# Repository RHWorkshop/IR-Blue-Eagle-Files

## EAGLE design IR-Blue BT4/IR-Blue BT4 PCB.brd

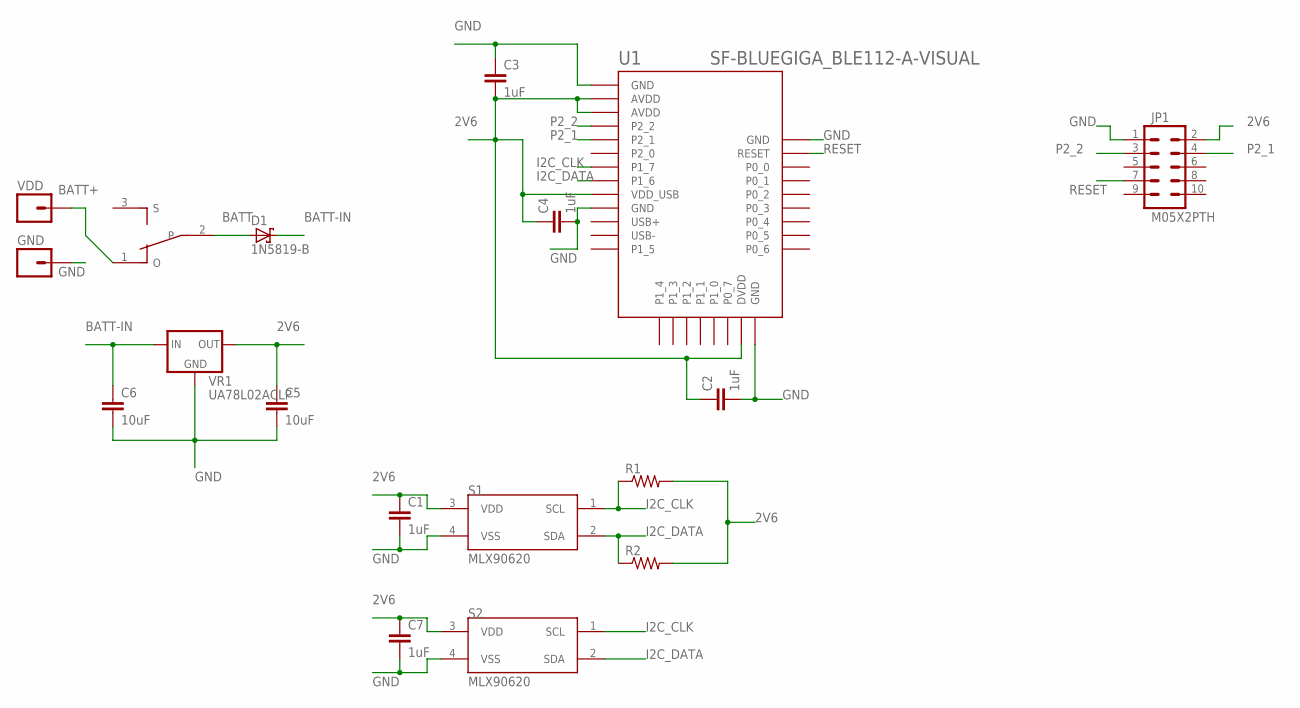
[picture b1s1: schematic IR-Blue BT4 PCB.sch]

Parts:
C1, C2, C3, C4, C7: 1uF; CAP-PTH-5MM
C5, C6: 10uF; CAP-PTH-5MM
D1: 1N5819-B; DO41-7.6
GND: M01PTH; 1X01
JP1: M05X2PTH; AVR_ICSP
R1, R2: RESISTORPTH-1/4W; AXIAL-0.4
S1, S2: MLX90620; TO-39
SW1: SMALL_SWITCH; EG1213
U1: SF-BLUEGIGA_BLE112-A-VISUAL; SF-BLUEGIGA_BLE112-A
VDD: M01PTH; 1X01
VR1: UA78L02ACLP; TO-92

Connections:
2V6: C1.1, C2.1, C3.2, C4.1, C5.1, C7.1, JP1.2, R1.P$2 (2), R2.P$2 (2), S1.3 (VDD), S2.3 (VDD), U1.AVDD1 (AVDD), U1.AVDD2 (AVDD), U1.DVDD, U1.VDD_USB, VR1.1 (OUT)
BATT: D1.A, SW1.2
BATT+: SW1.1 (O), VDD.1
BATT-IN: C6.1, D1.C, VR1.3 (IN)
GND: C1.2, C2.2, C3.1, C4.2, C5.2, C6.2, C7.2, GND.1, JP1.1, S1.4 (VSS), S2.4 (VSS), U1.GND1 (GND), U1.GND2 (GND), U1.GND3 (GND), U1.GND4 (GND), VR1.2 (GND)
I2C_CLK: R1.P$1 (1), S1.1 (SCL), S2.1 (SCL), U1.P1_7
I2C_DATA: R2.P$1 (1), S1.2 (SDA), S2.2 (SDA), U1.P1_6
P2_1: JP1.4, U1.P2_1
P2_2: JP1.3, U1.P2_2
RESET: JP1.7, U1.RESET

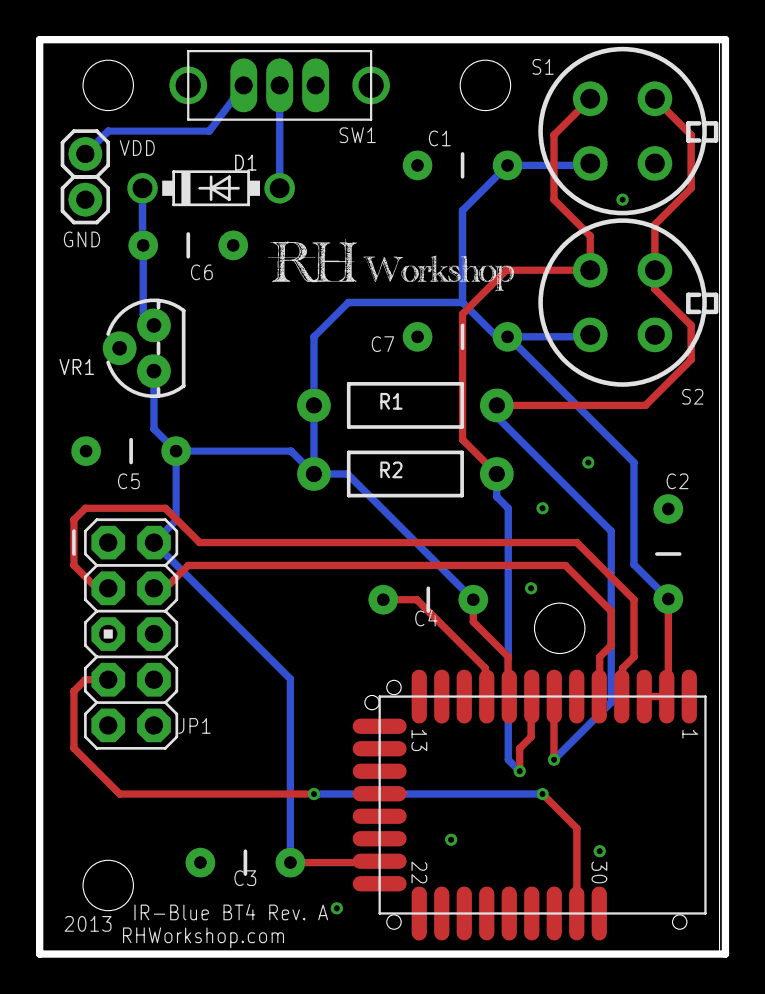
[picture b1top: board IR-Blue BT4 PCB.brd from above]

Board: 2 copper layers, 38.1 x 50.8 mm, 19 parts (0 on the bottom side), 10 nets.

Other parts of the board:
U$1: RH-LOGO

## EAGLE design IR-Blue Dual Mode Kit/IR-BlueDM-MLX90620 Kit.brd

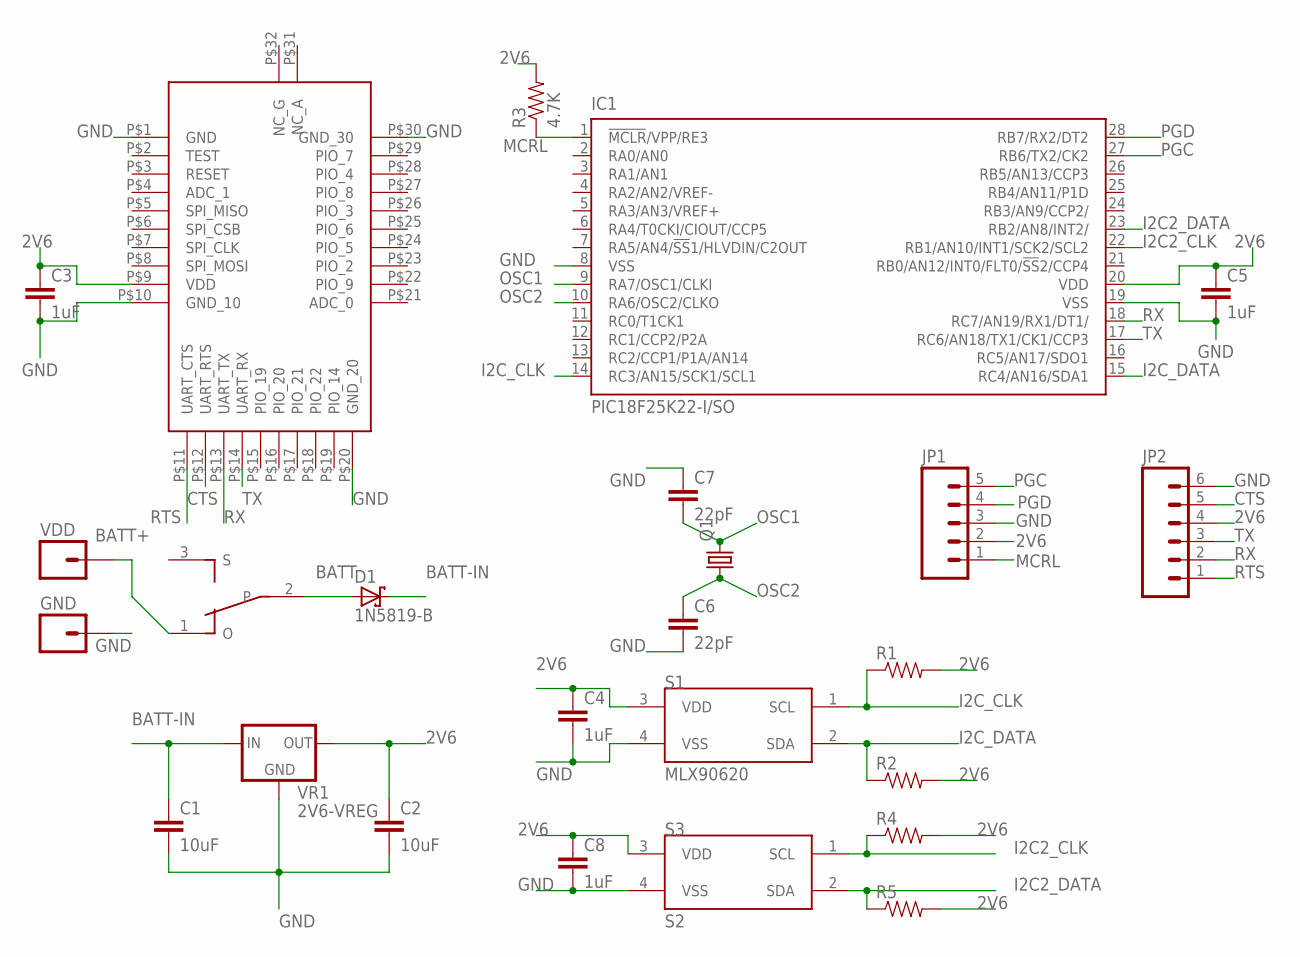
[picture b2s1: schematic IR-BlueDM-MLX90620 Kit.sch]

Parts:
C1, C2: 10uF; CAP-PTH-5MM
C3, C4, C5, C8: 1uF; CAP-PTH-5MM
C6, C7: 22pF; CAP-PTH-5MM
D1: 1N5819-B; DO41-7.6
GND: M01PTH; 1X01
IC1: PIC18F25K22-I/SO; SO28W
IC2: BR-LE4.0-D2A; BR-LE4.0-X2A
JP1: M05PTH; 1X05
JP2: M06SIP; 1X06
Q1: CRYSTALHC49S; HC49/S
R1, R2, R4, R5: RESISTORPTH-1/4W; AXIAL-0.4
R3: 4.7K; AXIAL-0.4
S1: MLX90620; TO-39
S2: SMALL_SWITCH; EG1213
S3: S2; TO-39
VDD: M01PTH; 1X01
VR1: 2V6-VREG; TO-92

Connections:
2V6: C2.1, C3.1, C4.1, C5.1, C8.1, IC1.20 (VDD), IC2.P$9 (VDD), JP1.2, JP2.4, R1.P$2 (2), R2.P$2 (2), R3.P$2 (2), R4.P$2 (2), R5.P$2 (2), S1.3 (VDD), S3.3 (VDD), VR1.1 (OUT)
BATT: D1.A, S2.2
BATT+: S2.1 (O), VDD.1
BATT-IN: C1.1, D1.C, VR1.3 (IN)
CTS: IC2.P$12 (UART_RTS), JP2.5
GND: C1.2, C2.2, C3.2, C4.2, C5.2, C6.2, C7.1, C8.2, GND.1, IC1.8 (VSS), IC1.19 (VSS), IC2.P$1 (GND), IC2.P$10 (GND_10), IC2.P$20 (GND_20), IC2.P$30 (GND_30), JP1.3, JP2.6, S1.4 (VSS), S3.4 (VSS), VR1.2 (GND)
I2C2_CLK: IC1.22 (RB1/AN10/INT1/SCK2/SCL2), R4.P$1 (1), S3.1 (SCL)
I2C2_DATA: IC1.23 (RB2/AN8/INT2/), R5.P$1 (1), S3.2 (SDA)
I2C_CLK: IC1.14 (RC3/AN15/SCK1/SCL1), R1.P$1 (1), S1.1 (SCL)
I2C_DATA: IC1.15 (RC4/AN16/SDA1), R2.P$1 (1), S1.2 (SDA)
MCRL: IC1.1 (!MCLR!/VPP/RE3), JP1.1, R3.P$1 (1)
OSC1: C7.2, IC1.9 (RA7/OSC1/CLKI), Q1.2
OSC2: C6.1, IC1.10 (RA6/OSC2/CLKO), Q1.1
PGC: IC1.27 (RB6/TX2/CK2), JP1.5
PGD: IC1.28 (RB7/RX2/DT2), JP1.4
RTS: IC2.P$11 (UART_CTS), JP2.1
RX: IC1.18 (RC7/AN19/RX1/DT1/), IC2.P$13 (UART_TX), JP2.2
TX: IC1.17 (RC6/AN18/TX1/CK1/CCP3), IC2.P$14 (UART_RX), JP2.3

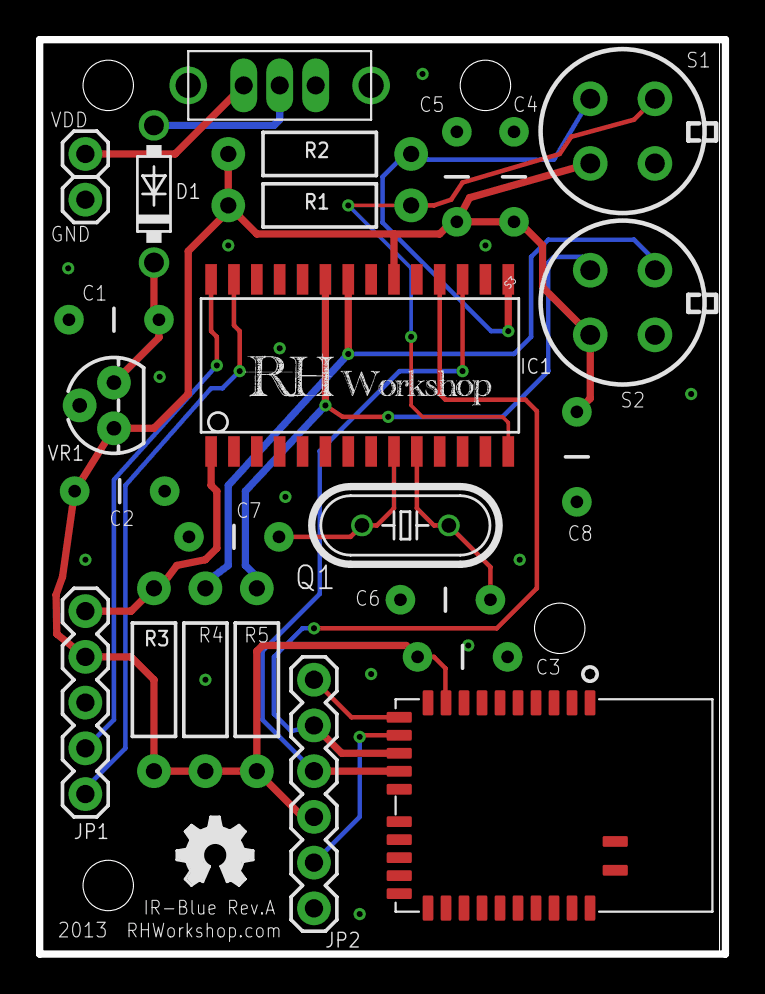
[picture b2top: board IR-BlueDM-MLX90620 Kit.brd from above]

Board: 2 copper layers, 38.1 x 50.8 mm, 27 parts (0 on the bottom side), 18 nets.

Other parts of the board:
U$1: RH-LOGO
U$2: OSHW_FILLX150_NOTEXT

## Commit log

2012-12-14 Initial Commit
    Not the final revision board but has been tested and works fine.
2013-01-28 Added IR-Blue PCB files
    Added PCB Files for Bluetooth 2 Only, Bluetooth 4 Only and Dual Mode
    Bluetooth boards.
2013-03-05 Added BOMs
2013-03-05 BOM Update
2013-03-05 Remove Extra BOM
2013-03-14 PIC Firmware for Dual Mode and BT2 modules
2013-04-24 Add missing User Libraries for Firmware

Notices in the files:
parts and their libraries:
SparkFun-Connectors: Licensing: CC v3.0 Share-Alike You are welcome to use this library for commercial purposes.
